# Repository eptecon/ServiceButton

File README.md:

ServiceButton: Connected Button for Notifications and Alarms
======

WiFi connected button that sends push notification data to an IoT platform. The notifications can be configured depending on use case.
Possible business cases are presented [here](/Docs).

### Hardware

ESP32 Microcontroller, simple push button, rechargeable battery.

### Firmware

The deevice connects with a server over WLAN. When button pressed, a notification message is composed from previously configured
data. The notification message is then sent in JSON format via TLS-secured MQTT protocol to the cloud service ([GlueLogics](https://github.com/eptecon/gluelogics)).

---

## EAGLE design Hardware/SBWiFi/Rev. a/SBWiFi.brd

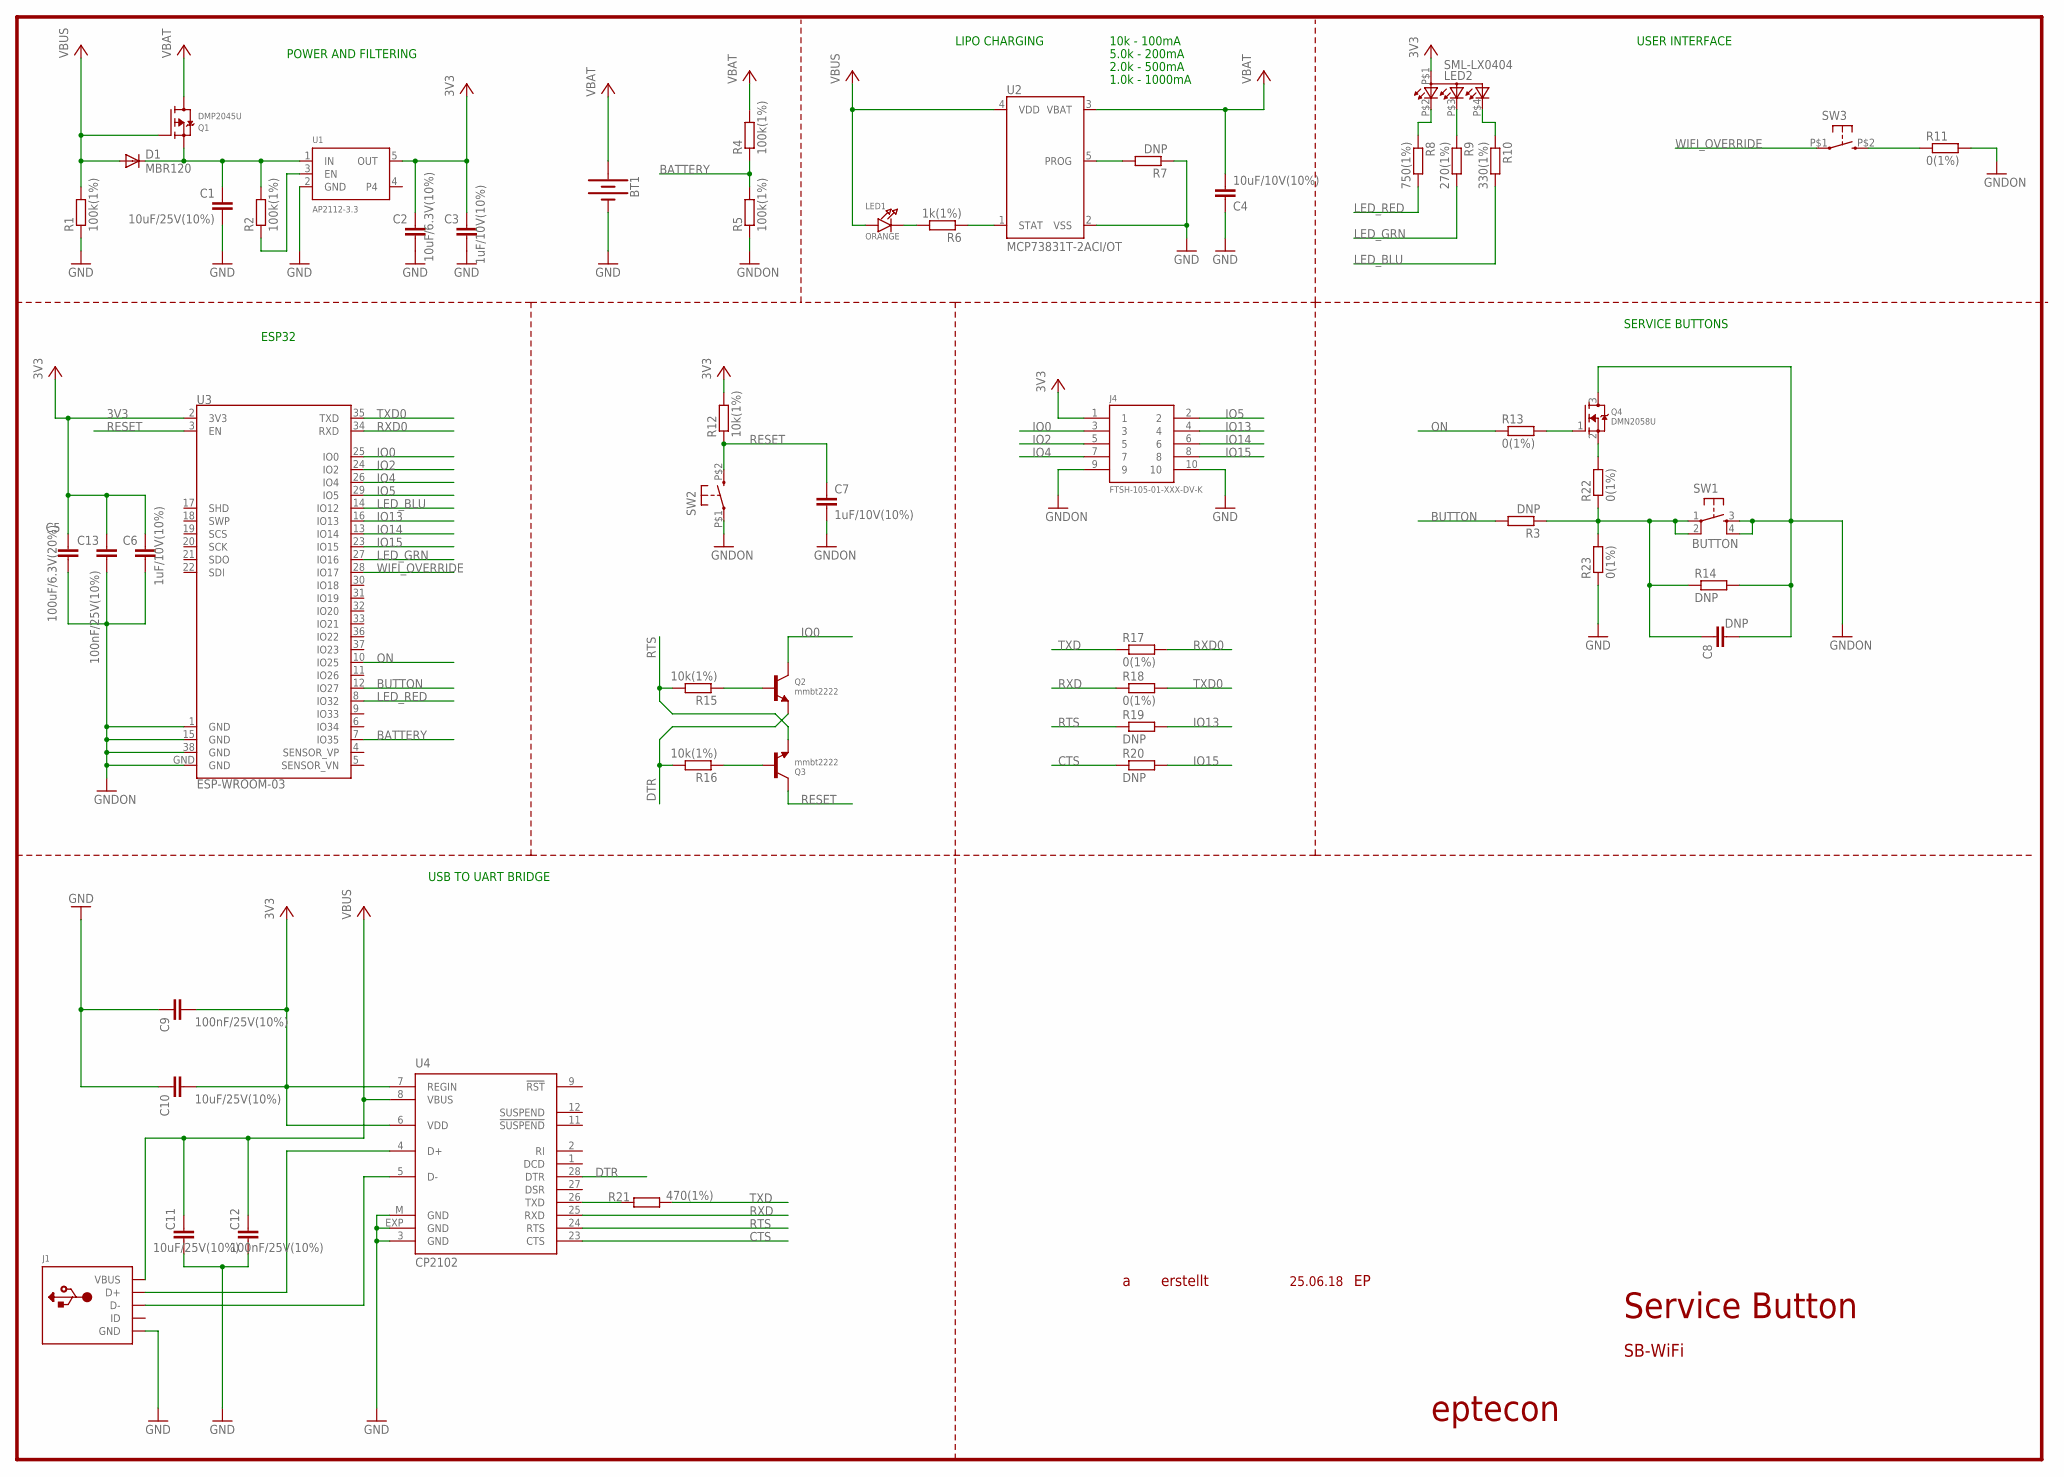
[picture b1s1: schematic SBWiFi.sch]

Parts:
BT1: BATTERY-AA
C1, C10, C11: 10uF/25V(10%); C0603
C2: 10uF/6.3V(10%); C0603
C3, C6, C7: 1uF/10V(10%); C0603
C4: 10uF/10V(10%); C0603
C5: 100uF/6.3V(20%); C0805
C8: DNP; C0603
C9, C12, C13: 100nF/25V(10%); C0603
D1: MBR120; SOD123
J1: USBMINIBLARGE; USB-MINIB_LARGER
J4: FTSH-105-01-XXX-DV-K
LED1: ORANGE; CHIPLED_0805_NOOUTLINE
LED2: SML-LX0404; LED_RGB
Q1: DMP2045U; SOT23-R
Q2, Q3: mmbt2222; SOT23-R
Q4: DMN2058U; SOT23-R
R1, R2, R4, R5: 100k(1%); R0603
R3, R7, R14, R19, R20: DNP; R0603
R6: 1k(1%); R0603
R8: 750(1%); R0603
R9: 270(1%); R0603
R10: 330(1%); R0603
R11, R13, R17, R18, R22, R23: 0(1%); R0603
R12, R15, R16: 10k(1%); R0603
R21: 470(1%); R0603
SW1: BUTTON; 7914G
SW2, SW3: SKTDLDE010-T-SWITCH; T-SWITCH-ALPS-2
U1: AP2112-3.3; SOT23-5
U2: MCP73831T-2ACI/OT; SOT23-5
U3: ESP-WROOM-03
U4: CP2102; MLP28

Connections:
3V3: C2.1, C3.1, C5.1, C6.1, C9.2, C10.2, C13.1, J4.1, LED2.P$1 (A2), R12.2, U1.5 (OUT), U3.2 (3V3), U4.6 (VDD), U4.7 (REGIN)
BATTERY: R4.1, R5.2, U3.7 (IO35)
BUTTON: R3.2, U3.12 (IO27)
CTS: R20.1, U4.23 (CTS)
DTR: Q2.2 (E), R16.2, U4.28 (DTR)
GND: BT1.GND@1 (-), C1.2, C2.2, C3.2, C4.1, C9.1, C10.1, C11.1, C12.1, J1.GND, J4.9, J4.10, R1.1, R5.1, R7.1, R11.2, R23.1, U1.2 (GND), U2.2 (VSS), U4.3 (GND), U4.EXP (GND), U4.M (GND)
GNDON: C5.2, C6.2, C7.2, C8.2, C13.2, Q4.3 (D), R14.2, SW1.3, SW1.4, SW2.P$1 (1), U3.1 (GND), U3.15 (GND), U3.38 (GND), U3.GND
IO0: J4.3, Q2.3 (C), U3.25 (IO0)
IO2: J4.5, U3.24 (IO2)
IO4: J4.7, U3.26 (IO4)
IO5: J4.2, U3.29 (IO5)
IO13: J4.4, R19.2, U3.16 (IO13)
IO14: J4.6, U3.13 (IO14)
IO15: J4.8, R20.2, U3.23 (IO15)
LED_BLU: R10.2, U3.14 (IO12)
LED_GRN: R9.2, U3.27 (IO16)
LED_RED: R8.2, U3.8 (IO32)
unnamed: LED2.P$2 (CRED), R8.1
unnamed: LED2.P$3 (CBLUE), R9.1
unnamed: LED2.P$4 (CGREEN), R10.1
unnamed: C8.1, R3.1, R14.1, R22.1, R23.2, SW1.1, SW1.2
unnamed: Q4.2 (S), R22.2
unnamed: Q4.1 (G), R13.2
unnamed: R2.1, U1.3 (EN)
unnamed: C1.1, D1.C, Q1.2 (S), R2.2, U1.1 (IN)
unnamed: Q3.1 (B), R16.1
unnamed: R21.1, U4.26 (TXD)
unnamed: Q2.1 (B), R15.1
unnamed: J1.D+, U4.4 (D+)
unnamed: J1.D-, U4.5 (D-)
unnamed: R11.1, SW3.P$2 (3)
unnamed: R6.1, U2.1 (STAT)
unnamed: LED1.C, R6.2
unnamed: R7.2, U2.5 (PROG)
ON: R13.1, U3.10 (IO25)
RESET: C7.1, Q3.3 (C), R12.1, SW2.P$2 (3), U3.3 (EN)
RTS: Q3.2 (E), R15.2, R19.1, U4.24 (RTS)
RXD: R18.1, U4.25 (RXD)
RXD0: R17.2, U3.34 (RXD)
TXD: R17.1, R21.2
TXD0: R18.2, U3.35 (TXD)
VBAT: BT1.PWR@1 (+), C4.2, Q1.3 (D), R4.2, U2.3 (VBAT)
VBUS: C11.2, C12.2, D1.A, J1.VBUS, LED1.A, Q1.1 (G), R1.2, U2.4 (VDD), U4.8 (VBUS)
WIFI_OVERRIDE: SW3.P$1 (1), U3.28 (IO17)

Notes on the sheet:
Service Button
SB-WiFi
eptecon
erstellt
25.06.18
ESP32
POWER AND FILTERING
USB TO UART BRIDGE
LIPO CHARGING
10k - 100mA
5.0k - 200mA
2.0k - 500mA
1.0k - 1000mA
USER INTERFACE
SERVICE BUTTONS

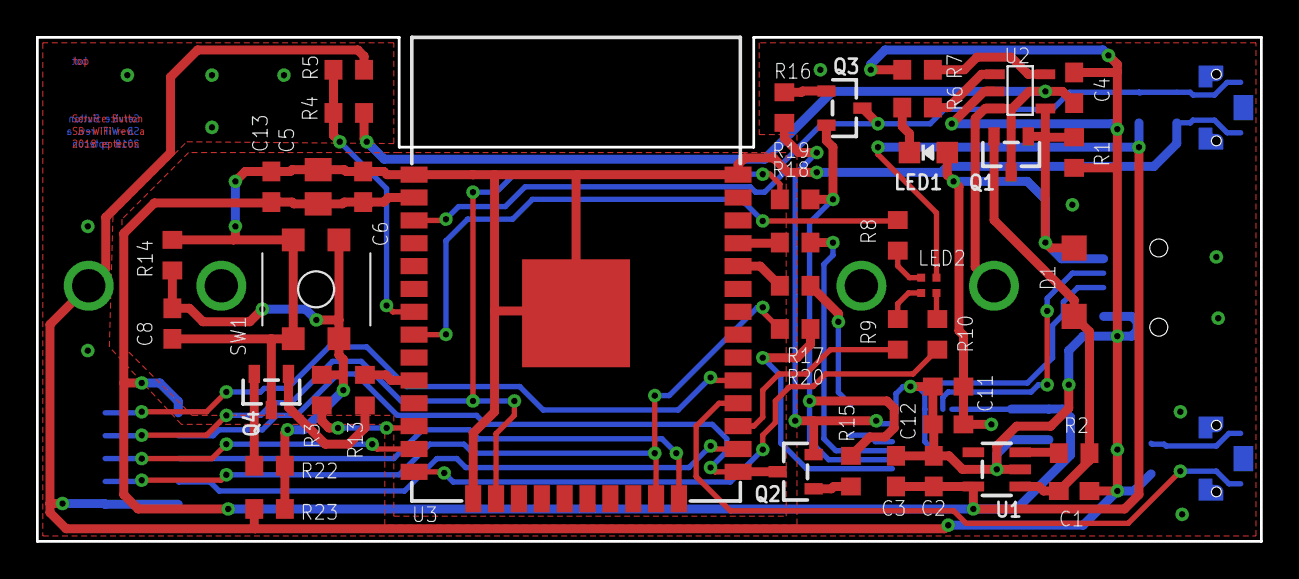
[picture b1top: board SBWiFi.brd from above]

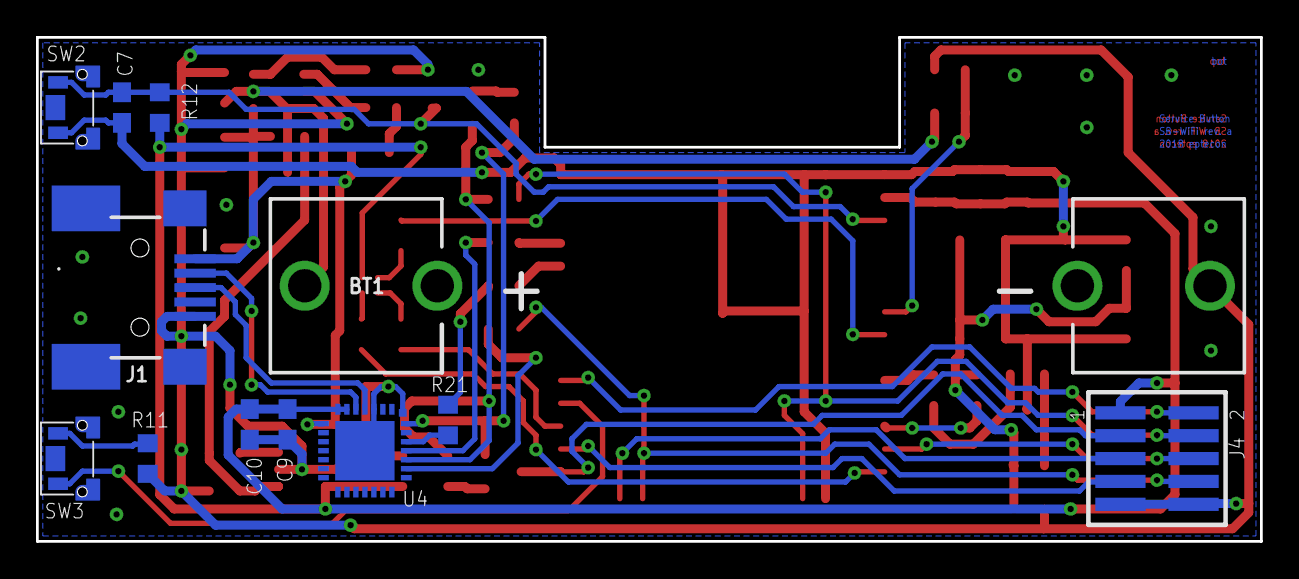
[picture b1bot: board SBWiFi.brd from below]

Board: 2 copper layers, 68.0 x 28.0 mm, 53 parts (12 on the bottom side), 44 nets.

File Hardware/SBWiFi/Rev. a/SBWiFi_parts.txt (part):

Stückliste exportiert aus /home/erwin/Projekte/eagle/ServiceButton/SBWiFi/Rev. a/SBWiFi.sch am 06.07.18 11:51

Part Value                Device               Package                Description                                                                                       MF      MPN       OC_FARNELL OC_NEWARK PROD_ID    SF_SKU   
BT1                       BATTERY-AA           BATTERY-AA             Battery - Single Cell                                                                                                                    BATT-08316 PRT-07949
C1   10uF/25V(10%)        C-EUC0603            C0603                  CAPACITOR, European symbol                                                                                                                                   
C2   10uF/6.3V(10%)       C-EUC0603            C0603                  CAPACITOR, European symbol                                                                                                                                   
C3   1uF/10V(10%)         C-EUC0603            C0603                  CAPACITOR, European symbol                                                                                                                                   
C4   10uF/10V(10%)        C-EUC0603            C0603                  CAPACITOR, European symbol                                                                                                                                   
C5   100uF/6.3V(20%)      C-EUC0805            C0805                  CAPACITOR, European symbol                                                                                                                                   
C6   1uF/10V(10%)         C-EUC0603            C0603                  CAPACITOR, European symbol                                                                                                                                   
C7   1uF/10V(10%)         C-EUC0603            C0603                  CAPACITOR, European symbol                                                                                                                                   
C8   DNP                  C-EUC0603            C0603                  CAPACITOR, European symbol                                                                                                                                   
C9   100nF/25V(10%)       C-EUC0603            C0603                  CAPACITOR, European symbol                                                                                                                                   
C10  10uF/25V(10%)        C-EUC0603            C0603                  CAPACITOR, European symbol                                                                                                                                   
C11  10uF/25V(10%)        C-EUC0603            C0603                  CAPACITOR, European symbol                                                                                                                                   
C12  100nF/25V(10%)       C-EUC0603            C0603                  CAPACITOR, European symbol                                                                                                                                   
C13  100nF/25V(10%)       C-EUC0603            C0603                  CAPACITOR, European symbol                                                                                                                                   
D1   MBR120               MBR0520LT            SOD123                 SCHOTTKY BARRIER RECTIFIER                                                                                                                                   
J1                        USBMINIBLARGE        USB-MINIB_LARGER       USB Connectors                                                                                                                                               
J4   FTSH-105-01-XXX-DV-K FTSH-105-01-XXX-DV-K FTSH-105-01-XXX-DV-K   0.05"x0.05" DOUBLE ROW SMT STRIP ASSEMBLY.                                                                                                                   
LED1 ORANGE               LED0805_NOOUTLINE    CHIPLED_0805_NOOUTLINE LED                                                                                                                                                          
LED2 SML-LX0404           SML-LX0404           LED_RGB                                                                                                                                                                             
Q1   DMP2045U             MOSFET-P             SOT23-R                P-Channel Mosfet                                                                                                                                             
Q2   mmbt2222             TRANSISTOR_NPN       SOT23-R                NPN Transistor                                                                                                                                               
Q3   mmbt2222             TRANSISTOR_NPN       SOT23-R                NPN Transistor                                                                                                                                               
Q4   DMN2058U             MOSFET-NREFLOW       SOT23-R                N-Channel Mosfet                                                                                                                                             
R1   100k(1%)             R-EU_R0603           R0603                  RESISTOR, European symbol                                                                                                                                    
R2   100k(1%)             R-EU_R0603           R0603                  RESISTOR, European symbol                                                                                                                                    
R3   DNP                  R-EU_R0603           R0603                  RESISTOR, European symbol                                                                                                                                    
R4   100k(1%)             R-EU_R0603           R0603                  RESISTOR, European symbol                                                                                                                                    
R5   100k(1%)             R-EU_R0603           R0603                  RESISTOR, European symbol                                                                                                                                    
R6   1k(1%)               R-EU_R0603           R0603                  RESISTOR, European symbol                                                                                                                                    
R7   DNP                  R-EU_R0603           R0603                  RESISTOR, European symbol                                                                                                                                    
R8   750(1%)              R-EU_R0603           R0603                  RESISTOR, European symbol                                                                                                                                    
R9   270(1%)              R-EU_R0603           R0603                  RESISTOR, European symbol                                                                                                                                    
R10  330(1%)              R-EU_R0603           R0603                  RESISTOR, European symbol                                                                                                                                    
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
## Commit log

2021-05-29 readme updated
2021-05-29 cleaning up
2021-05-29 update license
2021-05-29 readme update
2021-06-28 license added

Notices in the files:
parts and their libraries:
GeekAmmo: Licensing:Creative Commons ShareAlike 4.0 International - https://creativecommons.org/licenses/by-sa/4.0
microbuilder: This work is placed in the public domain, and may be freely used for commercial and non-commercial work with the following conditions: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
